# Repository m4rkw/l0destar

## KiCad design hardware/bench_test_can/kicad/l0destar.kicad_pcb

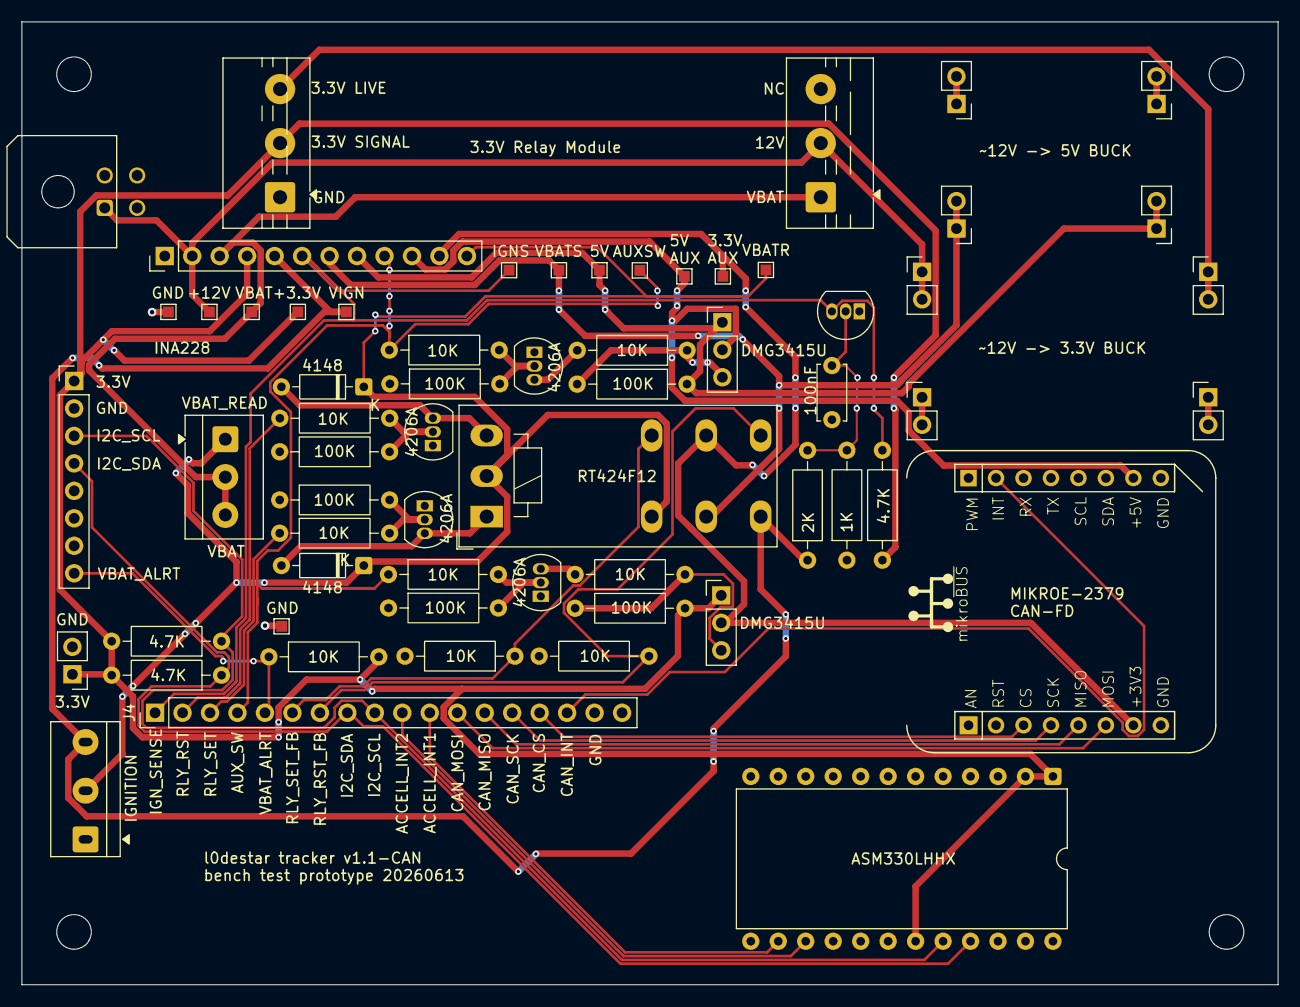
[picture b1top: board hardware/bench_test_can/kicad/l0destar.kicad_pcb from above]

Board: 2 copper layers, 116.2 x 89.0 mm, 66 parts (0 on the bottom side), 38 nets.

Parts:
CON1: MIKROBUS_HOST_CONN
H1, H2, H3, H4: MountingHole; MountingHole_3.2mm_M3
J2: Conn_01x12_Socket; PinHeader_1x12_P2.54mm_Vertical
J3: Conn_01x03_Pin; TerminalBlock_4Ucon_1x03_P3.50mm_Horizontal
J4: Conn_01x18_Socket; PinHeader_1x18_P2.54mm_Vertical
S1J1: Conn_01x04; Molex_Micro-Fit_3.0_43045-0400_2x02_P3.00mm_Horizontal
S1J2: Conn_01x02_Socket; PinHeader_1x02_P2.54mm_Vertical
S1R1, S1R2: 4.7K; R_Axial_DIN0207_L6.3mm_D2.5mm_P10.16mm_Horizontal
S1R3, S5R2, S5R3, S5R5, S5R6, S7R1, S7R3, S7R5, S7R7: 10K; R_Axial_DIN0207_L6.3mm_D2.5mm_P10.16mm_Horizontal
S2K1: Hoembpn_3V_Relay_Module
S3J1: INA228; PinHeader_1x08_P2.54mm_Vertical
S4C1: 100nF; C_Disc_D5.0mm_W2.5mm_P5.00mm
S4R1, S4R3: 56K; R_Axial_DIN0207_L6.3mm_D2.5mm_P10.16mm_Horizontal
S4R2, S5R1, S5R4, S7R2, S7R4, S7R6, S7R8: 100K; R_Axial_DIN0207_L6.3mm_D2.5mm_P10.16mm_Horizontal
S5D1, S5D2: 1N4148; D_DO-35_SOD27_P7.62mm_Horizontal
S5K1: RT424F12; Relay_DPDT_Schrack-RT2-FormC-Dual-Coil_RM5mm
S5Q1, S5Q2, S5Q3, S7Q1, S7Q3: ZVN4206A; TO-92_Inline
S6U1_J1, S6U1_J5: BUCK INPUT +; PinHeader_1x02_P2.54mm_Vertical
S6U1_J2, S6U1_J6: BUCK INPUT -; PinHeader_1x02_P2.54mm_Vertical
S6U1_J3, S6U1_J7: BUCK OUTPUT +; PinHeader_1x02_P2.54mm_Vertical
S6U1_J4, S6U1_J8: BUCK OUTPUT -; PinHeader_1x02_P2.54mm_Vertical
S7Q2, S7Q4: DMG3415U; DMG3415U_Breakout
S8U1: ASM330LHHXG1TR; DIP-24_W15.24mm
SW2: SW_SPDT; SPDT_Slide_Toggle_5mm
TP1, TP2, TP4, TP5, TP6, TP7, TP8, TP9, TP10, TP11, TP12, TP13, TP14: TestPoint; TestPoint_Pad_1.0x1.0mm

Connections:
+3.3V: J2.4, S1J2.1, S1R1.2, S1R2.2, S1R3.2, S2K1.IN (Pin_2), S3J1.1, S4R3.1, S7Q4.2 (S), S7R8.1, S8U1.1, S8U1.2, S8U1.19, TP8.1 (1_1)
+3.3V_AUX: CON1.P7 (3V3), J2.11, S5K1.21, S7Q4.3 (D), TP11.1 (1_1)
+3.3V_BUCK: S2K1.VCC (Pin_3), S6U1_J7.1, S6U1_J7.2
+5V: J2.8, S6U1_J3.1, S6U1_J3.2, S7Q2.2 (S), S7R4.1, TP10.1 (1_1)
+5V_AUX: CON1.P10 (5V), J2.10, S7Q2.3 (D), TP13.1 (1_1)
+12V: J2.2, S1J1.1, S2K1.COM (Pin_5), S6U1_J5.1, S6U1_J5.2, TP4.1 (1_1)
ACCELL_INT1: J4.11, S8U1.14
ACCELL_INT2: J4.10, S8U1.15
AUX_SW: J2.9, J4.4, S7R1.1, S7R5.1, TP7.1 (1_1)
CAN_CS: CON1.P3 (CS), J4.15
CAN_INT: CON1.P15 (INT), J4.16
CAN_MISO: CON1.P5 (MISO), J4.13
CAN_MOSI: CON1.P6 (MOSI), J4.12
CAN_SCK: CON1.P4 (SCK), J4.14
GND: CON1.P8 (GND1), CON1.P9 (GND2), J2.1, J4.17, J4.18, S1J1.2, S1J2.2, S2K1.GND (Pin_1), S3J1.2, S4C1.2, S4R2.1, S5Q1.1 (S), S5Q2.1 (S), S5Q3.1 (S), S5R1.1, S5R4.2, S5R5.2, S5R6.2, S6U1_J2.1, S6U1_J2.2, S6U1_J4.1, S6U1_J4.2, S6U1_J6.1, S6U1_J6.2, S6U1_J8.1, S6U1_J8.2, S7Q1.1 (S), S7Q3.1 (S), S7R2.1, S7R6.1, S8U1.13, S8U1.22, TP12.1 (1_1), TP14.1 (1_1)
I2C_SCL: J4.9, S1R1.1, S3J1.3, S8U1.20
I2C_SDA: J4.8, S1R2.1, S3J1.4, S8U1.21
IGN_SENSE: J2.6, J4.1, S4R3.2, S5Q3.3 (D), TP6.1 (1_1)
unnamed: S5D1.2 (A), S5K1.A1, S5Q1.3 (D)
unnamed: S5D2.2 (A), S5K1.A2, S5Q2.3 (D)
unnamed: S5Q1.2 (G), S5R1.2, S5R2.2
unnamed: S5Q2.2 (G), S5R3.2, S5R4.1
unnamed: S4C1.1, S4R1.2, S4R2.2, S5Q3.2 (G)
unnamed: S7Q1.3 (D), S7R3.2
unnamed: S7Q1.2 (G), S7R1.2, S7R2.2
unnamed: S7Q2.1 (G), S7R3.1, S7R4.2
unnamed: S7Q3.3 (D), S7R7.2
unnamed: S7Q3.2 (G), S7R5.2, S7R6.2
unnamed: S7Q4.1 (G), S7R7.1, S7R8.2
RLY_RST: J4.2, S5R3.1
RLY_RST_FB: J4.7, S5K1.24, S5R5.1
RLY_SET: J4.3, S5R2.1
RLY_SET_FB: J4.6, S5K1.22, S5R6.1
VBAT: J2.3, J3.2, J3.3, S2K1.NO (Pin_4), TP1.1 (1_1)
VBAT_ALRT: J4.5, S1R3.1, S3J1.8
VBAT_READ: J2.12, J3.1, S5D1.1 (K), S5D2.1 (K), S5K1.12, S5K1.A3, SW2.2 (B), TP5.1 (1_1)
VBAT_SWITCHED: J2.7, S5K1.11, S6U1_J1.1, S6U1_J1.2, TP9.1 (1_1)
VIGN: J2.5, S4R1.1, S5K1.14, SW2.3 (C), TP2.1 (1_1)

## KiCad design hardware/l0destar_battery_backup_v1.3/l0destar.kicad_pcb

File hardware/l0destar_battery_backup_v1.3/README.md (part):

# l0destar battery backup v1.3

## Overview

- This is a prototype inline battery backup module for the l0destar vehicle
  tracker. It sits in the harness between the car and the tracker and holds
  the tracker's supply at ~9V from a single CR123A lithium primary cell when
  car power is cut
- It is designed to be hand-solderable (hot air required). Every active part
  is in a leaded package: MSOP-12, SOT-23, TSOT-23, SC70, DPAK
- The cell is a **non-rechargeable** primary in a board-mounted holder.
  Nothing on the board charges it. See [Why a primary cell](#why-a-primary-cell)
- Pin-compatible with the v3.4 tracker's 2x3 Micro-Fit harness: J1 takes the
  car harness, J2 goes to the tracker, the CAN/K-line pins pass straight
  through and ignition passes through a diode (S1D1)
- 4-layer 63.1 x 36.2 mm board, JLC04161H-7628 stack-up, four M2 mounting
  holes. PCB DRC is clean and schematic ERC has only the cosmetic
  `endpoint_off_grid` warnings

## Changes from v1.2

1. Fix LM66100 pin connections to enable reverse current blocking

## Disclaimer

This is a prototype, not a product. Nothing here is validated or certified,
the parts lists are examples rather than a verified BOM, and every number
below is a desk calculation from datasheets rather than a bench measurement -
repeat the testing yourself rather than taking any of it on trust.

I strongly recommend not using unbranded CR123 cells or buying them from less
reputable sources.

**Before building or installing anything from this repository, read the
[full disclaimer](../../DISCLAIMER.md).**

## Test status

| Item | Test | Result | Notes |
|---------|------|--------|-------|
| Input stage | 12V car input reverse polarity | PASSED | S2Z1 conducts forward into S2F1, which should clear |
| Input stage | Pass-through drop VCAR to PPTRACKER, tracker asleep | PASSED | v1.0 dropped ~0.5V here. Expected ~20 mV, the LTC4412 regulated forward drop |
| Input stage | Pass-through drop VCAR to PPTRACKER at 50 mA and 250 mA | PASSED | Expected ~20 mV; S2Q1 is 15 mΩ so the regulation sets it, not R<sub>DS(on)</sub> |
| Switchover | Boost enables when the car rail falls below ~10.06V | PASSED | S6U1 with the 6.8M/909k divider |
| Switchover | Boost disables when the car rail returns above ~11V | PASSED | Depends on the cell voltage through S6R38/S6R39, see [Notes](#notes) |
| Boost | 9.6V output at S4C14/S4C15 | PASSED | 1.202V x (1 + 909k/130k) = 9.61V; ~9V at J2 after S2D2 |
| Cell | Reversed cell is harmless | PASSED | Not physically possible to install the cell backwards |
| Cell | No current ever flows into the cell | PASSED | Ammeter in series with the cell with the car present and during handover |
| Wake pulse | IGN pulse at boost start, car ignition wire connected and off | PASSED | Failed on v1.0. Expected ~12V peak, above 8V for ~0.4 s, at J2 pin 5, with S1D1 blocking the car pulldown |
| Wake pulse | Car ignition reaches the tracker | PASSED | J2 pin 5 should be one S1B drop below J1 pin 5 with the key on |
| Wake pulse | Sleeping tracker wakes and raises `backup power` | PASSED | Needs firmware with `CONFIG_APP_BACKUP_SUPPLY=y` |
| Board | Parked drain from the car with the cell fitted | PASSED | ~15 µA on top of the tracker's own draw |

## Features

 - Inline between the car harness and the tracker; CAN/K-line pass straight
   through, ignition through S1D1
 - ~15 µA quiescent draw from the car in pass-through: ~13 µA LTC4412HV plus
   the ~1.6 µA sense divider
 - Same input protection parts as the tracker: 2A time-lag fuse, 33V TVS
   sized to ride out suppressed load dump
 - Reverse polarity protection
 - Ideal diode pass-through (LTC4412HV + P-channel FET) with a ~20 mV drop
   down to sleep current
 - Synchronous boost (LTC3122) with true output disconnect: the backup rail
   is 0V while the car is present, so the cell is only ever loaded during a
   cut
 - Nanopower comparator switchover (TLV3012, 2.8 µA) running straight from
   the cell: takes over below ~10.06V on the car rail
 - No cell lockout: the boost runs the cell until it can't. It's a
   consumable primary, so there is nothing to protect
 - Ignition wake pulse: a cut wakes a sleeping tracker immediately instead of
   at its next timed wake, and the tracker reports the cut
 - Estimated runtime on a 1500 mAh CR123A: ~200 days idle, ~58 days
   reporting hourly, ~19 days reporting every 15 minutes
 - 3D-printable two-part enclosure with the cell accessible under the lid

## Why a primary cell

A non-rechargeable cell rather than a rechargeable pack, for three reasons:

- No rechargeable 18650-format cell is rated for storage in a sun-parked car.
  The binding limit is storage temperature (+45 °C at best for Li-ion and LFP;
  +20 °C beyond three months for LTO) and a parked car reaches ~70 °C cabin
  air. A CR123A is rated to +60/+70 °C
- Cycle life is not worth paying for. The backup cycles a handful of times a
  year
- A primary turns silent ageing into an event. The boost regulates its output,
  so the tracker cannot see cell voltage - a rechargeable's calendar fade would
  be invisible until a real theft tested it. The only thing that consumes a
  primary is a power cut the tracker already alerts on, so *"did it get
  used?"* is answered in the server's alert log

The cell is a consumable. A `backup power` alert that runs for a long time
means the cell needs replacing, since it does not recover. Taking the cell
out is the storage mode.

### Ignition wake pulse

A sleeping tracker has three wake sources: its timer, the accelerometer and
ignition-present. A power cut touches none of them, so on its own it would be
found at the next timed wake. The module therefore fakes ignition for a
moment when it takes over.

The tracker's wake is level-triggered and the firmware latches it, so the
pulse only has to trip the interrupt. On an ignition wake the firmware reads
the rail first: in the backup band it is the module's pulse, so the unit
reports at once with the `backup power` alert and goes back to sleep.

The car holds its ignition wire at ground when the key is off, which sank
the pulse on v1.0. S1D1 sits in series between the car's ignition (J1 pin 5)
and the tracker's (J2 pin 5) so the pulse only drives the tracker's input.
The cost is one silicon diode drop on the ignition signal the tracker sees.

Limits: a second cut within the ~40 s VBOOST decay gives no pulse and falls
back to the timed wake.

## Board configuration

### Connectors

Both connectors are the tracker's Molex Micro-Fit 3.0 2x3 (43045-0600) with
the v3.4 pinout. J1 is the car harness, J2 goes to the tracker.

| Pin | J1 (car) | J2 (tracker) | Notes |
|-----|----------|--------------|-------|
| 1 | SPARE | SPARE | Unused by v3.4, not connected on this board |
| 2 | GND | GND | |
| 3 | CAN\_H / K | CAN\_H / K | Passed straight through |
| 4 | +12V | +12V (PPTRACKER) | Car through the ideal diode, or ~9V from the boost on backup |
| 5 | IGN | IGN | Through S1D1 (one diode drop); the wake pulse is injected on the J2 side |
| 6 | CAN\_L / L | CAN\_L / L | Passed straight through |

### Firmware

The tracker needs `CONFIG_APP_BACKUP_SUPPLY=y`. With it, a supply between
`CONFIG_APP_BACKUP_MIN_MV` (8500) and `CONFIG_APP_BACKUP_MAX_MV` (9700) with
the ignition off is treated as backup power rather than a flat car battery:
timed reports keep going, the 11.8V power-off and 12.0V sleep-safety rules
are bypassed, a `backup power` alert is raised once and a `car power
restored` alert when the rail comes back. Without the module a car battery in
that band is flat, so leave it off on trackers that do not have one.

### Cell

The board carries a Keystone 1051 CR123A holder and nothing else as a cell
input. Fit a CR123A from one of the three big brands (Energizer 123 /
EL123AP, Panasonic CR123A, Duracell DL123A): all are high-rate Li-MnO2 cells,
1500-1550 mAh, rated for the ~130 mA typical / ~250 mA worst-case bursts the
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
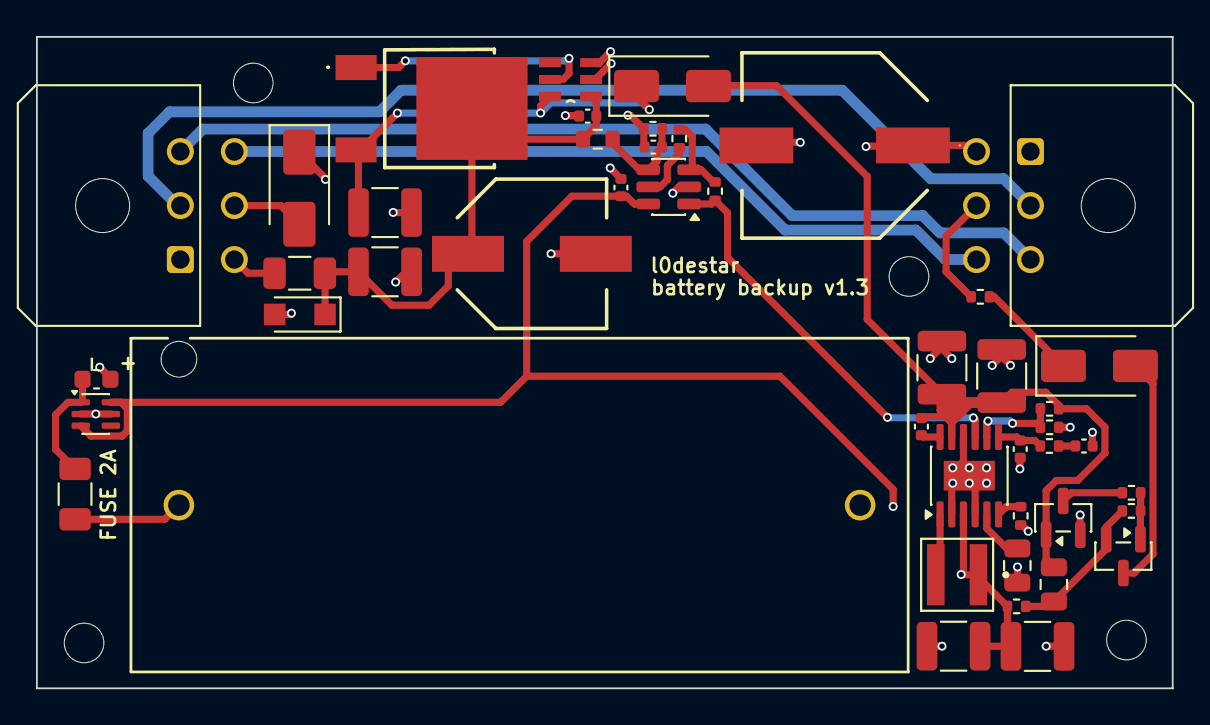
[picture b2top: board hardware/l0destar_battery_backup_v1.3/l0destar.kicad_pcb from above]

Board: 4 copper layers, 63.1 x 36.2 mm, 50 parts (0 on the bottom side), 30 nets.

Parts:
S1D1, S2D2, S5D3: S1B; D_SMA
S1H1, S1H2, S1H3, S1H4: MountingHole; MountingHole_2.2mm_M2
S1J1: Car harness; Molex_Micro-Fit_3.0_43045-0600_2x03_P3.00mm_Horizontal
S1J2: Tracker harness; Molex_Micro-Fit_3.0_43045-0600_2x03_P3.00mm_Horizontal
S2C1, S4C9, S6C2: 0402 100nF 50V 10% X7R; C_0402_1005Metric
S2C2: 47uF 63V - EEH-ZC1J470P; EEH_ZC1J470P
S2C4: 82uF 63V - HHXC630ARA820MJA0G; HHXC630ARA820MJA0G
S2C5, S2C6, S4C14, S4C15: 1210 10uF 50V X7R SOFT-TERM; C_1210_3225Metric
S2F1, S3F1: 0407002.WRA; Fuse_1206_3216Metric
S2Q1: SQD50P06-15L_GE3; SQD50P06-15L_GE3_tight
S2U1: LTC4412HVIS6PBF
S2Z1: PTVS33VS1UTR,115; Nexperia_CFP3_SOD-123W
S3BT1: CR123A; 1051_KEY
S3C1: 0603 2.2uF 25V 10% X7R; C_0603_1608Metric
S3U1: LM66100DCKR; SOT-363_SC-70-6
S4C7, S4C8: 1210 47uF 10V 20% X7R; C_1210_3225Metric
S4C11: 0402 560pF 50V 5% C0G/NP0; C_0402_1005Metric
S4C12: 0402 10pF 50V C0G/NP0; C_0402_1005Metric
S4C13, S5C17: 0805 4.7uF 50V 10% X7R; C_0805_2012Metric
S4L1: 2.2uH XFL4020-222MEC; IND_XFL4020-222ME
S4R14: 0402 57.6K 1%; R_0402_1005Metric
S4R18: 0402 200K 1%; R_0402_1005Metric
S4R19, S6R33: 0402 909K 1% ANTI-SULFUR AEC-Q200; R_0402_1005Metric
S4R20: 0402 130K 1%; R_0402_1005Metric
S4U5: LTC3122EMSE#PBF; MSOP-12-1EP_3x4.039mm_P0.65mm_EP1.651x2.845mm
S5Q6: 2N7002; SOT-23
S5Q7: BC856B; SOT-23
S5R21: 0402 10K 5%; R_0402_1005Metric
S5R22, S5R24, S5R25, S6R39: 0402 1M 1%; R_0402_1005Metric
S6C1: 0402 100pF 50V 5% C0G/NP0; C_0402_1005Metric
S6R32: 0603 6.8M 1%; R_0603_1608Metric
S6R38: 0402 47K 5%; R_0402_1005Metric
S6U1: TLV3012AIDBVR; SOT-23-6

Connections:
CAN_H: S1J1.3, S1J2.3
CAN_L: S1J1.6, S1J2.6
EN_BOOST: S4U5.9 (SD), S6R39.1, S6U1.1 (OUT)
GND: S1J1.1, S1J2.1, S2C1.2, S2C2.2 (-), S2C4.2 (-), S2C5.2, S2C6.2, S2U1.2 (GND), S2U1.3 (CTL), S2Z1.2 (A), S3BT1.2, S3C1.2, S3U1.2 (GND), S3U1.5 (ST), S4C7.2, S4C8.2, S4C11.2, S4C12.2, S4C13.2, S4C14.2, S4C15.2, S4R14.2, S4R20.2, S4U5.2 (PGND), S4U5.4 (PWM/SYNC), S4U5.10 (SGND), S4U5.13 (EP), S5Q6.2 (S), S6C1.2, S6C2.2, S6R33.2, S6U1.2 (V-)
IGN: S1D1.1 (K), S1J2.5, S5R21.2
IGN_CAR: S1D1.2 (A), S1J1.5
KWIRE_K: S1J1.2, S1J2.2
unnamed: S2Q1.1 (G), S2U1.5 (GATE)
unnamed: S3BT1.1, S3F1.1
unnamed: S3C1.1, S3F1.2, S3U1.1 (VIN)
unnamed: S4C11.1, S4R18.2
unnamed: S4C9.1, S4U5.12 (CAP)
unnamed: S4R19.2, S4R20.1, S4U5.8 (FB)
unnamed: S4R14.1, S4U5.6 (RT)
unnamed: S4L1.2, S4U5.1 (SW)
unnamed: S4C12.1, S4R18.1, S4U5.7 (VC)
unnamed: S4C13.1, S4U5.5 (VCC)
unnamed: S5D3.2 (A), S5Q7.3 (C)
unnamed: S5D3.1 (K), S5R21.1
unnamed: S5Q6.3 (D), S5R24.2
unnamed: S5Q7.1 (B), S5R24.1, S5R25.2
unnamed: S5C17.1, S5Q7.2 (E), S5R22.2, S5R25.1
unnamed: S6R38.2, S6R39.2, S6U1.3 (IN+)
unnamed: S6C1.1, S6R32.2, S6R33.1, S6U1.4 (IN-)
unnamed: S6R38.1, S6U1.5 (REF)
PP12V: S1J1.4, S2F1.1
PPTRACKER: S1J2.4, S2C4.1 (+), S2C5.1, S2D2.1 (K), S2Q1.3 (S), S2U1.6 (SENSE)
VBAT: S3U1.3 (~CE), S3U1.6 (VOUT), S4C7.1, S4C8.1, S4L1.1, S4U5.3 (VIN), S5R22.1, S6C2.1, S6U1.6 (V+)
VBOOST: S2D2.2 (A), S4C9.2, S4C14.1, S4C15.1, S4R19.1, S4U5.11 (VOUT), S5C17.2, S5Q6.1 (G)
VCAR: S2C1.1, S2C2.1 (+), S2C6.1, S2F1.2, S2Q1.2 (D), S2U1.1 (VIN), S2Z1.1 (K), S6R32.1

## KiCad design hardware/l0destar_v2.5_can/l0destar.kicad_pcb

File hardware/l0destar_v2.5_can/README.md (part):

# l0destar v2.5C (CAN-bus version)

## Overview

**NOTE: THIS HAS NOT YET BEEN TESTED, USE AT YOUR OWN RISK**

- This is a prototype l0destar vehicle tracker PCB designed to be
  hand-solderable (hot air required)
- It makes use of the [Makerdiary nRF9151 Connect Kit](https://makerdiary.com/products/nrf9151-connectkit) to provide the LTE and GPS
functions
- Component vias are dogleg-routed deliberately in order to keep the PCB costs
as low as possible
- The RF trace width is calculated using a standard 4-layer stackup at JLCPCB,
  different fabrication processes may require adjustment

## Disclaimer

This is a prototype, not a product. Nothing here is validated or certified,
the parts lists are examples rather than a verified BOM, and any test results
recorded below are my own unverified bench observations - repeat the testing
yourself rather than taking them on trust.

**Before building or installing anything from this repository, read the
[full disclaimer](../../DISCLAIMER.md).**

## Test status

| Item | Test | Result | Notes |
|---------|------|--------|-------|
| Input stage | 12V input reverse polarity | NOT TESTED | |
| Input stage | 12V ignition input reverse polarity | NOT TESTED | |
| INA228 | Voltage reading function | NOT TESTED |
| Ignition presence | Ignition sense 3.3v signal | NOT TESTED | |
| LT8609 | 4.2V output | NOT TESTED | |
| Auxillary 3.3V rail | Switches on enable signal | NOT TESTED | |
| Accelerometer | Operates while awake | NOT TESTED | |
| Accelerometer | Wake on motion | NOT TESTED | |
| GPS antenna bias tee | Obtains GPS signal | NOT TESTED | |
| CAN | Connectivity | NOT TESTED | |
| CAN standby via XSTBY signal | NOT TESTED | |
| Board | Quiescent current | NOT TESTED | Estimated at around 370 µA |

## Features

 - 12V live and 12V ignition inputs with TVS and reverse polarity protection
 - Ignition presence sensing
 - INA228 voltage reading
 - High efficiency buck converter
 - Auxillary 3.3V rail for the GPS antenna bias tee
 - ASM330LHHXG1TR 6-axis IMU gyro/accelerometer
 - USB-C can be connected and disconnected for programming without any power
   disruption
 - CAN bus interface

## Changes from the v1.1 mini prototype

 - Dramatically smaller PCB footprint
 - Switched to a 4-layer stackup for simpler routing (especially useful on the
   other two variants that have CAN and ISO-9141 circuits)
 - Components were resized from a default of 0805 to a new default of 0402 and
   only bumped to 0603 or 0805 where necessary for specification
 - The large aluminium polymer caps were removed
 - The buck output cap was replaced with 2x 1210 ceramic 220uF caps for
   dramatically lower ESR
 - Power consumption while asleep was optimised significantly with the estimated
   quiscent draw in sleep mode with the accelerometer armed at around 370 µA
 - The relay power control circuit was removed as the quiscent current is so low
   in sleep mode that it seems unnecessary. Anyone wanting to only power the
   unit when the ignition is on can just power the 12V rail directly from the
   ignition rail
 - More thought was given to the specifications of the components for automotive
   use and these are now indicated in the bill of materials
 - The input stage MOSFETs and TVS were tuned for smaller footprint and more
   appropriate specification for automotive use

## Power supply

The Connect Kit can be powered through VBUS which would be much simpler as it
can take 5V, but then you have to disconnect the power before connecting a USB
cable. Same for the Nordic dev board - they both explicitly say not to connect
powered USB and VBUS at the same time. Because the intention is to install this
in a vehicle for testing the pragmatic decision was taken to power it with a
4.2V buck feeding the battery connector. With this power connection we can
connect USB-C at any time to update the firmware without needing to disconnect
power.

## Bill of materials

| Item | Description | Specification | Example | Notes |
|------|-------------|---------------|---------|-------|
| MCU | MCU and GSM/GPS 40pin board | nRF9151 Connect Kit | [Makerdiary nRF9151 Connect Kit](https://makerdiary.com/products/nrf9151-connectkit) | |
| S1J1 | Molex Micro-fit 3.0 2x02 PCB connector | 43045-0400 | [43045-0400](https://uk.farnell.com/molex/43045-0400/conn-r-a-pcb-hdr-4pos-2row-3mm/dp/9733019) | | 
| S1J2 | Makerdiary header 1 | 20-pin 2.54mm header | [20-pin pcb header](https://amzn.to/44hTFGN) | |
| S1J3 | Makerdiary header 2 | 20-pin 2.54mm header | [20-pin pcb header](https://amzn.to/44hTFGN) | |
| S1R1 | I2C pull-up resistor | 0402 4.7K 1% | [MP003476](https://uk.farnell.com/multicomp-pro/mp003476/res-4k7-1-0-0625w-0402-thick-film/dp/3392645) | |
| S1R2 | I2C pull-up resistor | 0402 4.7K 1% | [MP003476](https://uk.farnell.com/multicomp-pro/mp003476/res-4k7-1-0-0625w-0402-thick-film/dp/3392645) | |
| S1C1 | 220uF buck output capacitor | 1210 220uF 6.3V 20% X5R | [GRM32ER60J227ME05K](https://uk.farnell.com/murata/grm32er60j227me05k/cap-220-f-6-3v-20-x5r-1210/dp/2671587) | Higher voltage/X7R spec is better if available |
| S1C2 | 220uF buck output capacitor | 1210 220uF 6.3V 20% X5R | [GRM32ER60J227ME05K](https://uk.farnell.com/murata/grm32er60j227me05k/cap-220-f-6-3v-20-x5r-1210/dp/2671587) | Higher voltage/X7R spec is better if available |
| S2Q1 | Reverse-polarity MOSFET | SQ2361 SOT-23 | [SQ2361ES-T1_GE3](https://uk.farnell.com/vishay/sq2361es-t1-ge3/mosfet-aec-q101-p-ch-60v-sot-23/dp/2889711) | |
| S2Q2 | Reverse-polarity MOSFET | SQ2361 SOT-23 | [SQ2361ES-T1_GE3](https://uk.farnell.com/vishay/sq2361es-t1-ge3/mosfet-aec-q101-p-ch-60v-sot-23/dp/2889711) | |
| S2D1 | 15V Zener diode | BZX84C15 | [BZX84C15](https://uk.farnell.com/multicomp-pro/bzx84c15/zener-diode-0-3w-15v-sot-23/dp/2675186) | |
| S2D2 | 400W TVS diode | PTVS33VS1UTR,115 SOD-123W | [PTVS33VS1UTR,115](https://uk.farnell.com/nexperia/ptvs33vs1utr-115/tvs-diode-aecq101-unidir-33v-400w/dp/3440137) | |
| S2D3 | 15V Zener diode | BZX84C15 | [BZX84C15](https://uk.farnell.com/multicomp-pro/bzx84c15/zener-diode-0-3w-15v-sot-23/dp/2675186) | |
| S2D4 | 400W TVS diode | PTVS33VS1UTR,115 SOD-123W | [PTVS33VS1UTR,115](https://uk.farnell.com/nexperia/ptvs33vs1utr-115/tvs-diode-aecq101-unidir-33v-400w/dp/3440137) | |
| S2R1 | Pulldown resistor | 0402 1% 1M | [ERJ2RKF1004X](https://uk.farnell.com/panasonic/erj2rkf1004x/res-1m-1-0-1w-0402-thick-film/dp/2302957) | |
| S2R2 | Pulldown resistor | 0402 1% 1M | [ERJ2RKF1004X](https://uk.farnell.com/panasonic/erj2rkf1004x/res-1m-1-0-1w-0402-thick-film/dp/2302957) | |
| S3U1 | INA228 voltage read IC | INA228 10-VSSOP | [INA228](https://www.aliexpress.com/item/1005008704299153.html) | |
| S3C1 | 1uF capacitor | 0402 >= 10V 10% X7R | [KAM05CR71A105KH](https://uk.farnell.com/kyocera-avx/kam05cr71a105kh/capacitor-mlcc-1uf-x7r-10v-0402/dp/4365709) | |
| S3C2 | 100nF capacitor | 0402 >= 25V 10% X7R | [MC0402B104K250CT](https://uk.farnell.com/multicomp-pro/mc0402b104k250ct/cap-0-1-f-25v-10-x7r-0402/dp/2320759) | |
| S4Q1 | Ignition sense MOSFET | 2N7002 SOT-23 | [2N7002](https://uk.farnell.com/multicomp-pro/2n7002/mosfet-n-ch-60v-0-115a-sot-23/dp/4295174) | |
| S4R1 | Ignition sense resistor | 0402 120K 1% | [RC0402FR-07120KL](https://uk.farnell.com/yageo/rc0402fr-07120kl/res-120k-1-0-063w-0402-thick-film/dp/9239480) | |
| S4R2 | Ignition sense resistor | 0402 47K 1% | [ERJ2RKF4702X](https://uk.farnell.com/panasonic/erj2rkf4702x/res-47k-1-0-1w-0402-thick-film/dp/2302806) | |
| S4R3 | Ignition sense resistor | 0402 56K 1% | [MCMR04X5602FTL](https://uk.farnell.com/multicomp-pro/mcmr04x5602ftl/res-56k-1-0-0625w-0402-ceramic/dp/2073131) | |
| S4C1 | 100nF capacitor | 0402 >= 25V 10% X7R | [MC0402B104K250CT](https://uk.farnell.com/multicomp-pro/mc0402b104k250ct/cap-0-1-f-25v-10-x7r-0402/dp/2320759) | |
| S6U1 | Buck converter | LT8609AIMSE MSOP-EP-10 | [LT8609AIMSE#PBF](https://uk.farnell.com/analog-devices/lt8609aimse-pbf/dc-dc-conv-sync-buck-2mhz-125deg/dp/4025049) | |
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
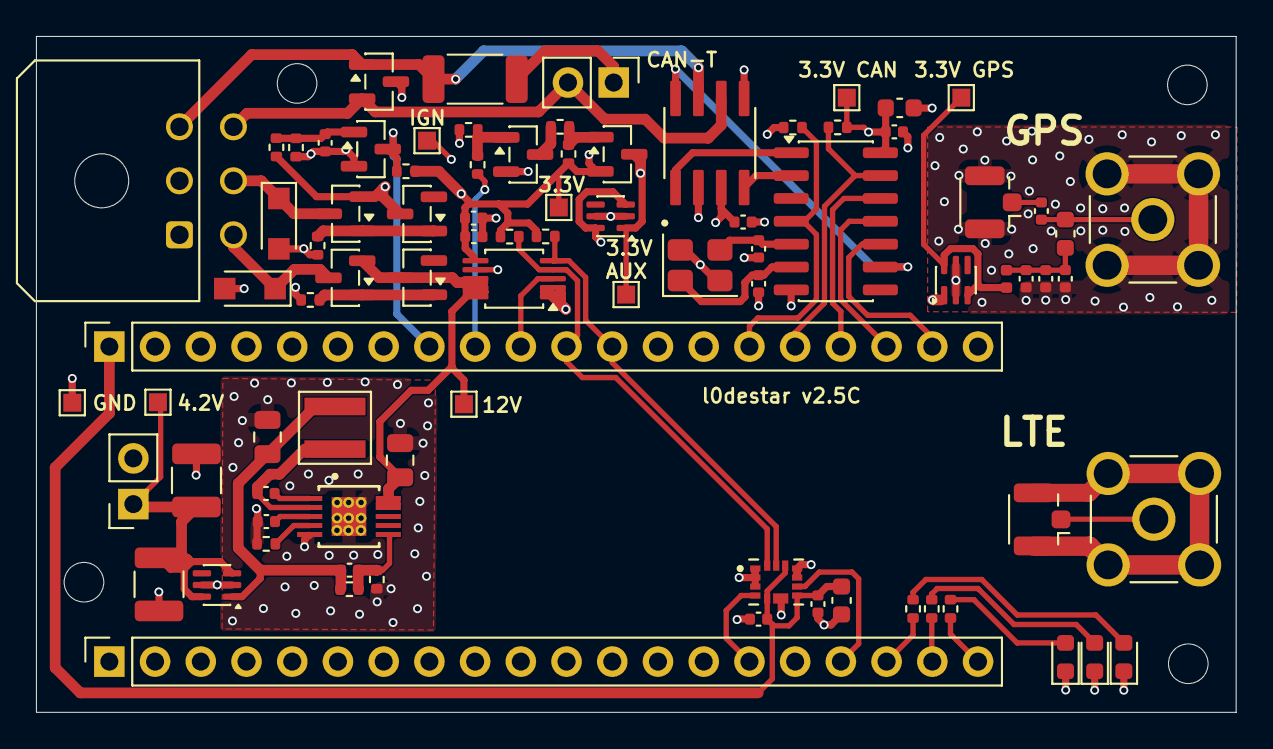
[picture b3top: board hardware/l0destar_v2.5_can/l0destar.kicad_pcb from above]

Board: 4 copper layers, 66.7 x 37.5 mm, 88 parts (0 on the bottom side), 52 nets.

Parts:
GND1: TestPoint; TestPoint_Pad_1.0x1.0mm
H1, H2, H3, H4: MountingHole; MountingHole_2.2mm_M2
PP3V3, PP3V3AUX1, PP3V3CAN1, PP3V3GPS2, PP4V5, PP12VIP1, PP12VP1: TestPoint; TestPoint_Pad_1.0x1.0mm
S1C1, S1C2: 220uF; C_1210_3225Metric
S1J1: Main connector; Molex_Micro-Fit_3.0_43045-0600_2x03_P3.00mm_Horizontal
S1J2: Conn_01x20_Socket; MakerDiary_nRF9151_ConnectKit_PinHeader_1-20
S1J3: Conn_01x20_Socket_21-40; MakerDiary_nRF9151_ConnectKit_PinHeader_21-40
S1J4: VCC; PinSocket_1x02_P2.54mm_Vertical
S1J5: CAN termination jumper; PinHeader_1x02_P2.54mm_Vertical
S1R1, S1R2: 4.7K; R_0402_1005Metric
S2D1, S2D3: BZX84C15; SOT-23
S2D2, S2D4: PTVS30VS1UTR,115; Nexperia_CFP3_SOD-123W
S2Q1, S2Q2: SQ2361; SOT-23
S2R1, S2R2, S6R3, S7R2: 1M; R_0402_1005Metric
S3C1, S6C2, S15C4: 1uF; C_0402_1005Metric
S3C2, S4C1, S6C1, S8C1, S8C3, S9C1, S9C4: 100nF; C_0402_1005Metric
S3U1: INA228; TSSOP-10_3x3mm_P0.5mm
S4Q1, S7Q1: 2N7002; SOT-23
S4R1: 120K; R_0402_1005Metric
S4R2: 47K; R_0402_1005Metric
S4R3: 56K; R_0402_1005Metric
S6C3: 4.7uF; C_0805_2012Metric
S6C4: 10pF; C_0402_1005Metric
S6C5: 22uF; C_0805_2012Metric
S6L1: XFL4020-222ME; IND_XFL4020-222ME
S6R1: 18.2K; R_0402_1005Metric
S6R2: 226K; R_0402_1005Metric
S6U1: LT8609AIMSE_PBF; LT8609AIMSE_WITH_GROUND_VIAS
S6U2, S9U3, S15U1: LM66100DCK; SOT-363_SC-70-6
S7Q2: DMG3415U; SOT-23
S7R1, S7R3: 100K; R_0402_1005Metric
S7R4: 470K; R_0402_1005Metric
S8C2, S9C5: 10uF; C_0603_1608Metric
S8U1: ASM330LHHXTR; XDCR_ASM330LHHXTR
S9C2, S9C3: 27pF; C_0402_1005Metric
S9D1: NUP2105L; SOT-23
S9R1, S9R2: 10K; R_0402_1005Metric
S9R3: 120R; R_2010_5025Metric
S9U1: TCAN334GDR
S9U2: MCP2518FD-xQBB; SOIC-14_3.9x8.7mm_P1.27mm
S9Y1: ABM8G-40.000MHZ-18-D2Y-T; Crystal_SMD_3225-4Pin_3.2x2.5mm
S13D1, S13D2, S13D3: LED; LED_0603_1608Metric
S13R1, S13R2, S13R3: 1K; R_0402_1005Metric
S15C1, S15C2: 100pF; C_0402_1005Metric
S15C3: 10nF; C_0402_1005Metric
S15FB1: 600R; L_0402_1005Metric
S15J1: GPS_UFL; U.FL_Hirose_U.FL-R-SMT-1_Vertical
S15J2: GPS_SMA; SAMTEC_SMA-J-P-H-RA-TH1
S15J3: GSM_UFL; U.FL_Hirose_U.FL-R-SMT-1_Vertical
S15J4: GSM_SMA; SAMTEC_SMA-J-P-H-RA-TH1
S15L1: 47-100 nH, SRF > 2 GHz; L_0603_1608Metric

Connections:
ACCELL_INT1: S1J2.15, S8U1.4 (INT1)
ACCELL_INT2: S1J2.17, S8U1.9 (INT2)
AUX_ENABLE: S1J3.32 (Pin_9), S7R1.1
CAN_CS: S1J3.25 (Pin_16), S9R1.2, S9U2.13 (~CS)
CAN_H: S1J1.3, S9D1.1 (K), S9R3.2, S9U1.7 (CANH)
CAN_INT: S1J3.26 (Pin_15), S9R2.2, S9U2.4 (~INT)
CAN_L: S1J1.6, S1J5.2, S9D1.2 (K), S9U1.6 (CANL)
CAN_SCK: S1J3.22 (Pin_19), S9U2.10 (SCK)
CAN_SDI: S1J3.23 (Pin_18), S9U2.11 (SDI)
CAN_SDO: S1J3.24 (Pin_17), S9U2.12 (SDO)
GND: GND1.1 (1_1), S1C1.2, S1C2.2, S1J1.2, S1J2.3 (GND), S1J3.39 (Pin_2), S1J4.2, S2D2.2 (A), S2D4.2 (A), S2R1.2, S2R2.2, S3C1.1, S3C2.1, S3U1.1 (A1), S3U1.2 (A0), S3U1.7 (GND), S4C1.2, S4Q1.2 (S), S4R2.1, S6C2.2, S6C3.2, S6C5.2, S6R1.2, S6R2.2, S6U1.5 (SYNC), S6U1.11 (GND), S6U2.2 (GND), S6U2.5 (ST), S7Q1.2 (S), S7R2.1, S8C1.2, S8C2.2, S8C3.2, S8U1.1 (SDO/SA0), S8U1.2 (MSDA), S8U1.3 (MSCL), S8U1.6 (NC), S8U1.7 (GND), S8U1.10 (NC), S8U1.11 (NC), S9C1.2, S9C2.2, S9C3.2, S9C4.2, S9C5.2, S9D1.3 (A), S9U1.2 (GND), S9U1.5 (SHDN), S9U2.7 (VSS), S9U3.2 (GND), S9U3.5 (ST), S9Y1.2 (G), S9Y1.4 (G), S13D1.1 (K), S13D2.1 (K), S13D3.1 (K), S15C2.2, S15C3.2, S15C4.2, S15J1.2 (Ext), S15J2.2, S15J2.3, S15J2.4, S15J2.5, S15J3.2 (Ext), S15J4.2, S15J4.3, S15J4.4, S15J4.5, S15U1.2 (GND), S15U1.5 (ST)
I2C_SCL: S1J3.29 (Pin_12), S1R2.1, S3U1.5 (SCL), S8U1.13 (SCL)
I2C_SDA: S1J3.30 (Pin_11), S1R1.1, S3U1.4 (SDA), S8U1.14 (SDA)
IGN_SENSE: S1J3.33 (Pin_8), S4Q1.3 (D), S4R3.2
INA_ALRT: S1J3.31 (Pin_10), S3U1.3 (~Alert)
LED1: S1J2.20, S13R1.2
LED2: S1J2.19, S13R2.2
LED3: S1J2.18, S13R3.2
unnamed: S1J5.1, S9R3.1
unnamed: S2D1.1 (A), S2Q1.1 (G), S2R1.1
unnamed: S2D3.1 (A), S2Q2.1 (G), S2R2.1
unnamed: S4C1.1, S4Q1.1 (G), S4R1.2, S4R2.2
unnamed: S6C1.1, S6U1.1 (BST)
unnamed: S6C4.1, S6R2.1, S6R3.1, S6U1.6 (FB)
unnamed: S6C2.1, S6U1.3 (INTVCC)
unnamed: S6R1.1, S6U1.4 (RT)
unnamed: S6C1.2, S6L1.1, S6U1.2 (SW)
unnamed: S6C4.2, S6C5.1, S6L1.2, S6R3.2, S6U2.1 (VIN)
unnamed: S7Q1.3 (D), S7R3.2
unnamed: S7Q1.1 (G), S7R1.2, S7R2.2
unnamed: S7Q2.1 (G), S7R3.1, S7R4.2
unnamed: S9U1.4 (RXD), S9U2.2 (RXCAN)
unnamed: S9U1.8 (STB), S9U2.9 (~INT0/GPIO0/XSTBY)
unnamed: S9U1.1 (TXD), S9U2.1 (TXCAN)
unnamed: S9C3.1, S9U2.6 (OSC1), S9Y1.1
unnamed: S9C2.1, S9U2.5 (OSC2), S9Y1.3
unnamed: S13D1.2 (A), S13R1.1
unnamed: S13D2.2 (A), S13R2.1
unnamed: S13D3.2 (A), S13R3.1
unnamed: S15C2.1, S15C3.1, S15C4.1, S15FB1.2, S15L1.1
unnamed: S15C1.1, S15J1.1 (In)
unnamed: S15J3.1 (In), S15J4.1
PP3V3: PP3V3.1 (1_1), S1J3.40 (Pin_1), S1R1.2, S1R2.2, S3C1.2, S3C2.2, S3U1.6 (VS), S4R3.1, S7Q2.2 (S), S7R4.1, S8C1.1, S8C2.1, S8C3.1, S8U1.5 (VDD_IO), S8U1.8 (VDD), S8U1.12 (CS)
PP3V3_AUX: PP3V3AUX1.1 (1_1), S7Q2.3 (D), S9U3.1 (VIN), S15U1.1 (VIN)
PP3V3_CAN: PP3V3CAN1.1 (1_1), S9C1.1, S9C4.1, S9C5.1, S9R1.1, S9R2.1, S9U1.3 (VCC), S9U2.14 (VDD), S9U3.3 (~CE), S9U3.6 (VOUT)
PP3V3_GPS: PP3V3GPS2.1 (1_1), S15FB1.1, S15U1.3 (~CE), S15U1.6 (VOUT)
PP4V2: PP4V5.1 (1_1), S1C1.1, S1C2.1, S1J4.1, S6U2.3 (~CE), S6U2.6 (VOUT)
PP12V: S1J1.4, S2D4.1 (K), S2Q2.3 (D)
PP12VI: S1J1.5, S2D2.1 (K), S2Q1.3 (D)
PP12VIP: PP12VIP1.1 (1_1), S2D1.3 (K), S2Q1.2 (S), S4R1.1
PP12VP: PP12VP1.1 (1_1), S2D3.3 (K), S2Q2.2 (S), S3U1.8 (Vbus), S3U1.9 (Vin-), S3U1.10 (Vin+), S6C3.1, S6U1.9 (VIN), S6U1.10 (EN/UV)
RF: S15C1.2, S15J2.1, S15L1.2

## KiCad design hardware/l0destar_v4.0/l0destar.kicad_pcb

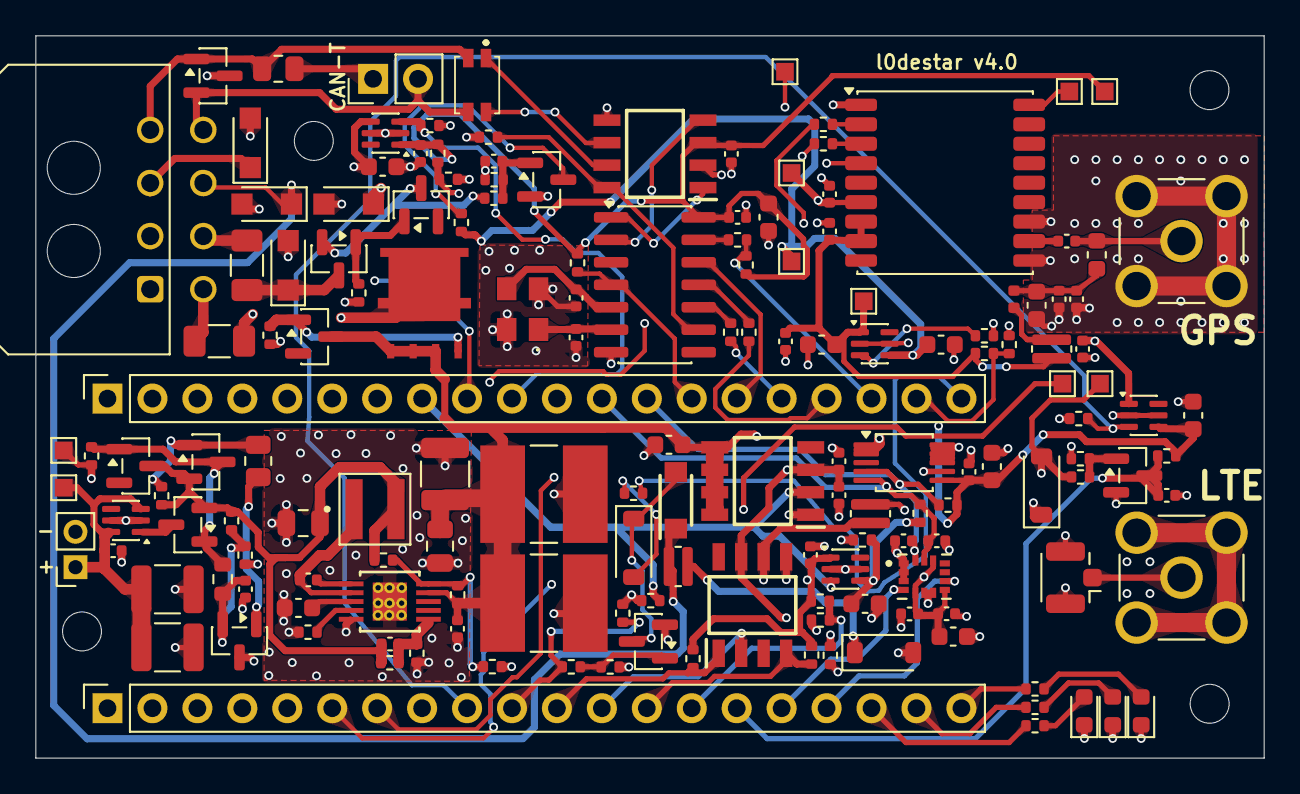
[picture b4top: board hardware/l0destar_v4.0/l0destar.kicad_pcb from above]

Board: 4 copper layers, 69.4 x 40.8 mm, 165 parts (0 on the bottom side), 91 nets.

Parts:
H1, H2, H3, H4: MountingHole; MountingHole_2.2mm_M2
S1C1, S3C2, S4C1, S6C1, S6C8, S7C2, S7C4, S7C9, S8C1, S8C3, S9C1, S9C4, S10C1, S16C2, S16C4, S16C5: 0402 100nF 50V 10% X7R; C_0402_1005Metric
S1J1: Main connector; Molex_Micro-Fit_3.0_43045-0800_2x04_P3.00mm_Horizontal
S1J2: Conn_01x20_Socket; MakerDiary_nRF9151_ConnectKit_PinHeader_1-20_tight
S1J3: Conn_01x20_Socket_21-40; MakerDiary_nRF9151_ConnectKit_PinHeader_21-40
S1J4: +; MakerDiary2PinHeader
S1R1, S1R2: 0402 1.8K 1%; R_0402_1005Metric
S1R3, S1R4, S1R5, S2R2, S7R3, S7R6, S7R7, S7R8, S10R6, S16R1, S16R4: 0402 100K 5%; R_0402_1005Metric
S2C1, S2C2: 47uF 2220 50V 20% X7R; CAPC6050X550N
S2C3: 10uF 1210 50V 10% X7R SOFT TERMINATION; C_1210_3225Metric
S2D1, S2D3, S11D1: BZX84C15; SOT-23
S2D2, S2D4, S10D2, S10D4: PTVS33VS1UTR,115; Nexperia_CFP3_SOD-123W
S2F1, S2F2: 0407002.WRA; Fuse_1206_3216Metric
S2Q1, S11Q1: SQ2361CES-T1_BE3; SOT-23
S2Q2: SQJ457EP-T1_BE3; POWERPAK-SO-8-4
S2R1, S7R4, S7R9, S16R5: 0402 1M 5%; R_0402_1005Metric
S3C1, S6C2, S7C1, S7C3, S7C8, S15C4, S16C1, S16C3: 0603 2.2uF 25V 10% X7R; C_0603_1608Metric
S3U1: INA238; TSSOP-10_3x3mm_P0.5mm
S4Q1, S7Q1, S10Q1: 2N7002; SOT-23
S4R1, S7R5: 0402 180K 5%; R_0402_1005Metric
S4R2, S4R3: 0402 56K 5%; R_0402_1005Metric
S6C3: 0805 4.7uF 50V 10% X7R; C_0805_2012Metric
S6C4: 0402 10pF 50V C0G/NP0; C_0402_1005Metric
S6C5: 0805 22uF 10V 20% X7R; C_0805_2012Metric
S6L1: XFL4020-222ME; IND_XFL4020-222ME
S6R1: 0402 18.2K 1%; R_0402_1005Metric
S6R2: 0402 226K 1% ANTI-SULFUR AEC-Q200; R_0402_1005Metric
S6R3, S10R9, S11R5: 0402 1M 1% ANTI-SULFUR AEC-Q200; R_0402_1005Metric
S6R4: 0402 0R JUMPER OR 1M 1% ANTI-SULFUR AEC-Q200; R_0402_1005Metric
S6R5: DNP 0402 243K 1% ANTI-SULFUR AEC-Q200; R_0402_1005Metric
S6R6: DNP 0402 3.92M 1%; R_0402_1005Metric
S6U1: LT8609AIMSE_PBF; LT8609AIMSE_WITH_GROUND_VIAS
S7C5, S7C7: 0402 1nF 50V 10% X7R; C_0402_1005Metric
S7C6: 0603 220nF 50V 10% X7R; C_0603_1608Metric
S7U1, S7U2, S7U4, S16U1: SiP32431DR3; SOT-363_SC-70-6
S7U3: ITS4060SSJNXUMA1
S8C2, S9C5: 0603 10uF 10V 20% X7R; C_0603_1608Metric
S8C4, S8C5, S15C2: 0402 100pF 50V 5% C0G/NP0; C_0402_1005Metric
S8R1: 0402 FB BLM15AG601SH1D; R_0402_1005Metric
S8U1: ASM330LHHXTR; XDCR_ASM330LHHXTR
S9C2, S9C3: 0402 27pF 10V 5% C0G/NP0; C_0402_1005Metric
S9D1: NUP2105L; SOT-23
S9FL1: ACT1210-101-2P-TL00; ACT12101012PTL00_tight
S9J1: Conn_01x02_Pin; PinHeader_1x02_P2.54mm_Vertical_Tight
S9R1, S9R2, S9R4, S10R1, S10R2, S10R5: 0402 10K 5%; R_0402_1005Metric
S9R3: 0805 120R 5% 0.5W; R_0805_2012Metric
S9R5, S13R1, S13R2, S13R3, S16R2, S16R3: 0402 1K 5%; R_0402_1005Metric
S9R6, S9R7: 0402 220R 5%; R_0402_1005Metric
S9U1: TCAN3414DR; SOIC127P600X175-8N
S9U2: MCP2518FD-xQBB; SOIC-14_3.9x8.7mm_P1.27mm
S9Y1: ECS-400-18-33-JGN-TR3; ECS4001833JGNTR3
S10D1, S10D3, S10D5: 1N4148W; D_SOD-123
S10R3, S10R4: 0508 510R 5% 1W; R_0508_1220Metric_WideTerminal_Tight
S10R7, S10R8: 0402 47K 5%; R_0402_1005Metric
S10U1: TJA1027T_20,118; TJA1027T_20_118
S10U2: AL5809-90P1-7
S11C1, S11C2: 1210 47uF 10V 20% X7R; C_1210_3225Metric
S11C3: 0402 3.3pF 50V C0G/NP0 +/- 0.25pF; C_0402_1005Metric
S11Q2: BC856BLT1G; SOT-23
S11R1: 0402 10K 1%; R_0402_1005Metric
S11R2: 0402 1M 1%; R_0402_1005Metric
S11R3: 0603 33M 5%; R_0603_1608Metric
S11R4: 0805 15K 1% ANTI-SULFUR AEC-Q200; R_0805_2012Metric
S11R6: 0402 1.05M 1%; R_0402_1005Metric
S11U1: LM66100DCK; SOT-363_SC-70-6
S11U2: ATL431BQDBZR; SOT-23
S12TP1: GND; TestPoint_Pad_1.0x1.0mm
S12TP2: 4.2V protected; TestPoint_Pad_1.0x1.0mm
S12TP3: 3.3V; TestPoint_Pad_1.0x1.0mm
S12TP4: 3.3V GNSS BCKP; TestPoint_Pad_1.0x1.0mm
S12TP5: 3.3V CAN; TestPoint_Pad_1.0x1.0mm
S12TP6: 3.3V K; TestPoint_Pad_1.0x1.0mm
S12TP7: 12V K; TestPoint_Pad_1.0x1.0mm
S13D1, S13D2, S13D3: Wurth 150060RS86000; LED_0603_1608Metric
S15C1: 0402 47pF 50V 5% C0G/NP0; C_0402_1005Metric
S15C3: 0402 10nF 50V 5% C0G/NP0; C_0402_1005Metric
S15FB1: 0402 600R 0.5A 25%; L_0402_1005Metric
S15J2: GPS_SMA; SAMTEC_SMA-J-P-H-RA-TH1_centrepin
S15J3: GSM_UFL; U.FL_Hirose_U.FL-R-SMT-1_Vertical
S15J4: GSM_SMA; SAMTEC_SMA-J-P-H-RA-TH1_centrepin
S15L1: LQW18AN68NJ00D; L_0603_1608Metric
S15R1: 0508 1W 5% 15R; R_0508_1220Metric_WideTerminal_Tight
S16TP1: 3.3V GNSS; TestPoint_Pad_1.0x1.0mm
S16TP2: SAFEBOOT_N; TestPoint_Pad_1.0x1.0mm
S16TP3: TIMEPULSE; TestPoint_Pad_1.0x1.0mm
S16U2: MAX-M10S; ublox_MAX

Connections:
ACCELL_INT1: S1J2.16, S8U1.4 (INT1)
ACCELL_INT2: S1J2.17, S8U1.9 (INT2)
CAN_CS: S1J3.23 (Pin_18), S9R1.2, S9R5.1
CAN_ENABLE: S1J3.31 (Pin_10), S1R4.2, S7U2.3 (ON)
CAN_H: S1J1.4, S9D1.1 (K), S9FL1.2, S9R3.2
CAN_INT: S1J3.27 (Pin_14), S9R2.2, S9U2.4 (~INT)
CAN_L: S1J1.8, S9D1.2 (K), S9FL1.3, S9J1.2
CAN_SCK: S1J3.25 (Pin_16), S9R6.1
CAN_SDI: S1J3.24 (Pin_17), S9R7.1
CAN_SDO: S1J3.26 (Pin_15), S9U2.12 (SDO)
GND: S1C1.1, S1J1.2, S1J2.3 (GND), S1J3.39 (Pin_2), S1J4.2, S1R3.1, S1R4.1, S1R5.1, S2C1.2, S2C2.2, S2C3.2, S2D2.2 (A), S2D4.2 (A), S2R1.2, S2R2.2, S3C1.1, S3C2.1, S3U1.1 (A1), S3U1.2 (A0), S3U1.7 (GND), S4C1.2, S4Q1.2 (S), S4R2.1, S6C2.2, S6C3.2, S6C5.2, S6C8.2, S6R1.2, S6R2.2, S6R5.1, S6U1.5 (SYNC), S6U1.11 (GND), S7C1.2, S7C2.2, S7C3.2, S7C4.2, S7C5.2, S7C6.2, S7C7.2, S7C8.2, S7C9.2, S7Q1.2 (S), S7R4.1, S7R6.1, S7R9.1, S7U1.2 (GND), S7U1.5 (GND), S7U2.2 (GND), S7U2.5 (GND), S7U3.1 (GND), S7U4.2 (GND), S7U4.5 (GND), S8C1.2, S8C2.2, S8C3.2, S8C4.2, S8C5.2, S8U1.1 (SDO/SA0), S8U1.2 (MSDA), S8U1.3 (MSCL), S8U1.6 (NC), S8U1.7 (GND), S9C1.2, S9C2.2, S9C3.2, S9C4.2, S9C5.2, S9D1.3 (A), S9R4.2, S9U1.2 (GND), S9U1.5 (SHDN), S9U2.7 (VSS), S9Y1.2 (GND_1), S9Y1.4 (GND_2), S10C1.1, S10D2.2 (A), S10D4.2 (A), S10Q1.2 (S), S10R5.2, S10R6.1, S10R9.1, S10U1.5 (GND), S11C1.2, S11C2.2, S11C3.1, S11R2.1, S11R6.1, S11U1.2 (GND), S11U1.5 (ST), S11U2.3 (ANODE), S12TP1.1 (1_1), S13D1.1 (K), S13D2.1 (K), S13D3.1 (K), S15C2.2, S15C3.2, S15C4.2, S15J2.2, S15J2.3, S15J2.4, S15J2.5, S15J3.2 (Ext), S15J4.2, S15J4.3, S15J4.4, S15J4.5, S16C1.2, S16C2.2, S16C3.2, S16C4.2, S16C5.2, S16R1.2, S16R5.2, S16U1.2 (GND)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
GNSS_BCKP_EN: S1J2.9, S1R3.2, S7U1.3 (ON)
GNSS_ENABLE: S1J2.8, S16R1.1, S16U1.3 (ON)
GNSS_RF: S15C1.1, S16U2.11 (RF_IN)
GNSS_RX: S1J2.6, S16R2.1
GNSS_TIMEPULSE: S1J2.7, S16TP3.1 (1_1), S16U2.4 (TIMEPULSE)
GNSS_TX: S1J2.5 (P9), S16R3.1
I2C_SCL: S1J3.29 (Pin_12), S1R2.1, S3U1.5 (SCL), S8C5.1, S8U1.13 (SCL)
I2C_SDA: S1J3.28 (Pin_13), S1R1.1, S3U1.4 (SDA), S8C4.1, S8U1.14 (SDA)
IGN_SENSE: S1J3.32 (Pin_9), S4Q1.3 (D), S4R3.2
KWIRE_K: S1J1.3, S10D2.1 (K), S10R3.2, S10U1.6 (LIN)
KWIRE_L: S1J1.7, S10D4.1 (K), S10R4.2, S10U2.1 (IN)
K_ENABLE: S1J3.33 (Pin_8), S1R5.2, S7U3.2 (IN), S7U4.3 (ON)
K_RX: S1J2.11, S10R1.2, S10U1.1 (RXD)
K_SLEEP: S1J2.12, S10R6.2, S10U1.2 (SLP_N)
K_TX: S1J2.13, S10R2.2, S10U1.4 (TXD)
LED1: S1J2.18, S13R1.2
LED2: S1J2.19, S13R2.2
LED3: S1J2.20, S13R3.2
L_SEND: S1J2.10, S10R5.1, S10R7.1
L_SENSE: S1J3.21 (Pin_20), S10R8.1
unnamed: S2D1.1 (A), S2Q1.1 (G), S2R1.1
unnamed: S2D2.1 (K), S2F1.1, S2Q1.3 (D)
unnamed: S2D3.1 (A), S2Q2.4, S2R2.1
unnamed: S2D4.1 (K), S2F2.2, S2Q2.5_0, S2Q2.5_1, S2Q2.5_2, S2Q2.5_3
unnamed: S4C1.1, S4Q1.1 (G), S4R1.2, S4R2.2
unnamed: S6C1.1, S6U1.1 (BST)
unnamed: S6R4.1, S6R5.2, S6R6.2, S6U1.10 (EN/UV)
unnamed: S6C4.1, S6R2.1, S6R3.1, S6U1.6 (FB)
unnamed: S6C2.1, S6U1.3 (INTVCC)
unnamed: S6R1.1, S6U1.4 (RT)
unnamed: S6C1.2, S6L1.1, S6U1.2 (SW)
unnamed: S7Q1.1 (G), S7R5.2, S7R6.2
unnamed: S8C1.1, S8C2.1, S8C3.1, S8R1.2, S8U1.5 (VDD_IO), S8U1.8 (VDD), S8U1.12 (CS)
unnamed: S9J1.1, S9R3.1
unnamed: S9FL1.1, S9U1.7 (CANH)
unnamed: S9FL1.4, S9U1.6 (CANL)
unnamed: S9U1.4 (RXD), S9U2.2 (RXCAN)
unnamed: S9R4.1, S9U1.8 (STBY), S9U2.9 (~INT0/GPIO0/XSTBY)
unnamed: S9U1.1 (TXD), S9U2.1 (TXCAN)
unnamed: S9C3.1, S9U2.6 (OSC1), S9Y1.1 (IN/OUT)
unnamed: S9C2.1, S9U2.5 (OSC2), S9Y1.3 (OUT/IN)
unnamed: S9R6.2, S9U2.10 (SCK)
unnamed: S9R7.2, S9U2.11 (SDI)
unnamed: S9R5.2, S9U2.13 (~CS)
unnamed: S10D1.1 (K), S10R3.1
unnamed: S10D3.1 (K), S10R4.1
unnamed: S10D5.2 (A), S10R8.2
unnamed: S10D5.1 (K), S10Q1.3 (D), S10U2.2 (OUT)
unnamed: S10Q1.1 (G), S10R7.2, S10R9.2
unnamed: S11D1.1 (A), S11Q1.1 (G), S11Q2.3, S11R2.2, S11R3.2
unnamed: S11Q2.1, S11R1.1, S11R4.2
unnamed: S11R4.1, S11U2.1 (CATHODE)
unnamed: S11C3.2, S11R3.1, S11R5.2, S11R6.2, S11U2.2 (REF)
unnamed: S13D1.2 (A), S13R1.1
unnamed: S13D2.2 (A), S13R2.1
unnamed: S13D3.2 (A), S13R3.1
unnamed: S15C2.1, S15C3.1, S15C4.1, S15FB1.2, S15L1.1
unnamed: S15FB1.1, S15R1.1
unnamed: S15J3.1 (In), S15J4.1
unnamed: S16R3.2, S16U2.3 (RXD)
unnamed: S16R2.2, S16U2.2 (TXD)
unnamed: S16TP2.1 (1_1), S16U2.18 (~SAFEBOOT)
PP3V3: S1J3.40 (Pin_1), S1R1.2, S1R2.2, S3C1.2, S3C2.2, S3U1.6 (VS), S4R3.1, S7C1.1, S7C3.1, S7C8.1, S7R7.2, S7U1.4 (IN), S7U2.4 (IN), S7U4.4 (IN), S8R1.1, S12TP3.1 (1_1), S16C1.1, S16U1.4 (IN)
PP3V3_CAN: S7C4.1, S7R3.1, S7U2.1 (OUT), S9C1.1, S9C4.1, S9C5.1, S9R1.1, S9R2.1, S9U1.3 (VDD), S9U2.14 (VDD), S12TP5.1 (1_1)
PP3V3_CAN_ST: S1J3.30 (Pin_11), S7R3.2, S7R4.2
PP3V3_GNSS: S15R1.2, S16C2.1, S16C3.1, S16C4.1, S16R4.1, S16TP1.1 (1_1), S16U1.1 (OUT), S16U2.7 (VCC_IO), S16U2.8 (VCC)
PP3V3_GNSS_BCKP: S7C2.1, S7U1.1 (OUT), S12TP4.1 (1_1), S16C5.1, S16U2.6 (V_BCKP)
PP3V3_GNSS_ST: S1J3.22 (Pin_19), S16R4.2, S16R5.1
PP3V3_K: S7C9.1, S7R8.1, S7U4.1 (OUT), S10R1.1, S10R2.1, S12TP6.1 (1_1)
PP3V3_K_ST: S1J2.14, S7R8.2, S7R9.2
PP4V2: S1C1.2, S1J4.1, S11C1.1, S11C2.1, S11U1.3 (~CE), S11U1.6 (VOUT), S12TP2.1 (1_1)
PP4V2_OVP_PROTECTED: S11Q1.3 (D), S11U1.1 (VIN)
PP4V2_UNPROTECTED: S6C4.2, S6C5.1, S6L1.2, S6R3.2, S6R6.1, S11D1.3 (K), S11Q1.2 (S), S11Q2.2, S11R1.2, S11R5.1
PP12V: S1J1.5, S2F2.1
PP12VI: S1J1.6, S2F1.2
PP12VIP: S2D1.3 (K), S2Q1.2 (S), S4R1.1
PP12VP: S2C1.1, S2C2.1, S2C3.1, S2D3.3 (K), S2Q2.1, S2Q2.2, S2Q2.3, S3U1.8 (Vbus), S3U1.9 (Vin-), S3U1.10 (Vin+), S6C3.1, S6C8.1, S6R4.2, S6U1.9 (VIN), S7C6.1, S7U3.5 (VS_1), S7U3.6 (VS_2), S7U3.7 (VS_3), S7U3.8 (VS_4)
PP12V_K: S7C5.1, S7R5.1, S7U3.3 (OUT), S10C1.2, S10D1.2 (A), S10D3.2 (A), S10U1.7 (VBAT), S12TP7.1 (1_1)
PP12V_K_ST: S1J2.15, S7C7.1, S7Q1.3 (D), S7R7.1
RF: S15C1.2, S15J2.1, S15L1.2
